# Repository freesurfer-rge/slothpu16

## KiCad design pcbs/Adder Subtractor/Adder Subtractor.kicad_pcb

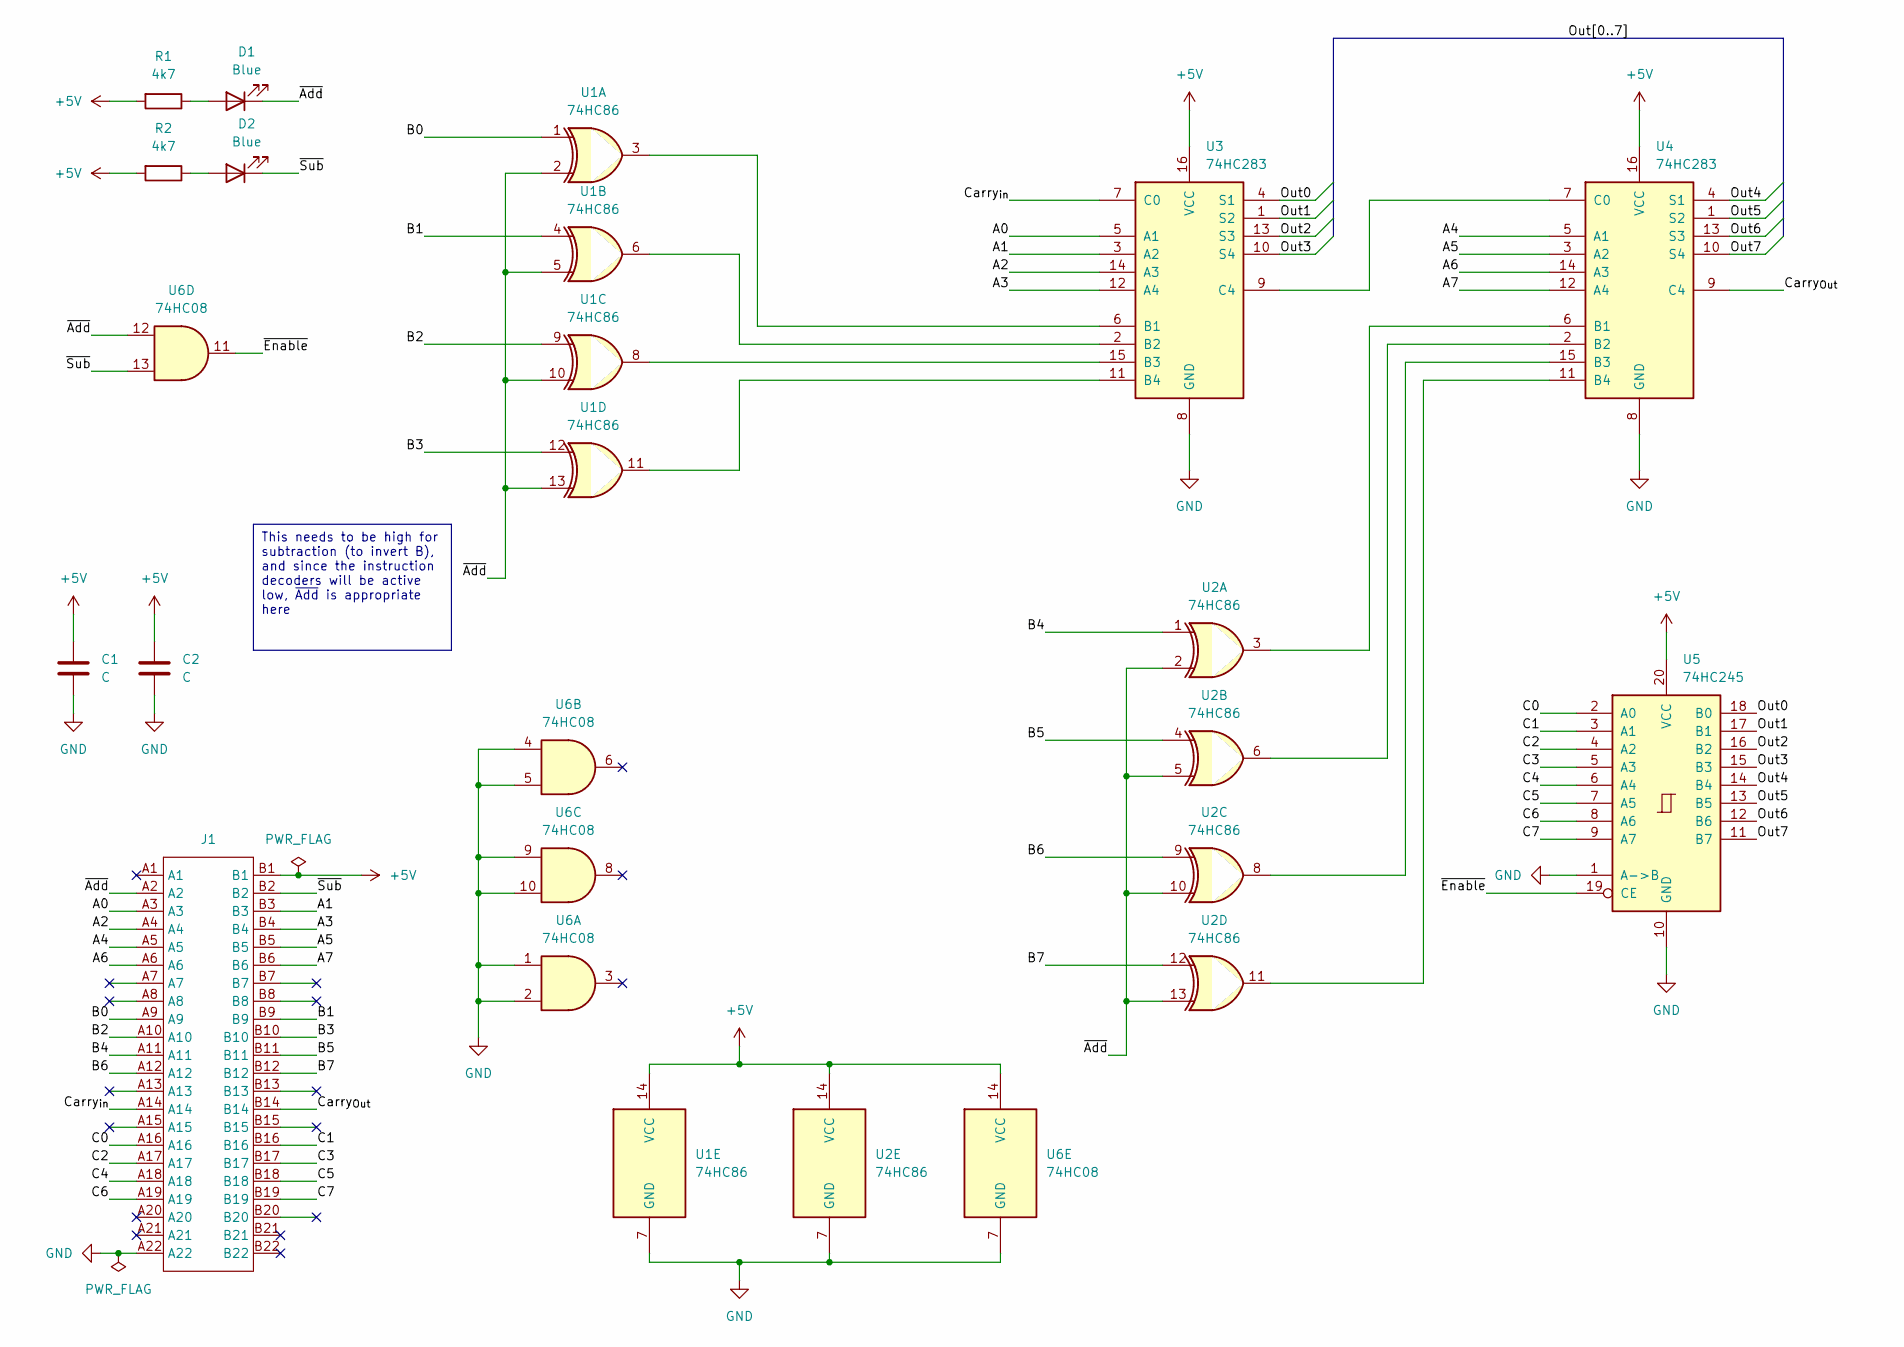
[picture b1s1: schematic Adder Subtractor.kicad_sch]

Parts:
C1, C2: C; C_0603_1608Metric; LCSC C14663
D1, D2: Blue; LED_0603_1608Metric; LCSC C72041
J1: TE-5530843-4-Edge
R1, R2: 4k7; R_0603_1608Metric; LCSC C23162
U1, U2: 74HC86; DIP-14_W7.62mm_Socket
U3, U4: 74HC283; DIP-16_W7.62mm_Socket
U5: 74HC245; SOIC-20W_7.5x12.8mm_P1.27mm; LCSC C5625
U6: 74HC08; SOIC-14_3.9x8.7mm_P1.27mm; LCSC C5593

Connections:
+5V: C1.1, C2.1, J1.B1, R1.2, R2.2, U1.14 (VCC), U2.14 (VCC), U3.16 (VCC), U4.16 (VCC), U5.20 (VCC), U6.14 (VCC)
/A0: J1.A3, U3.5 (A1)
/A1: J1.B3, U3.3 (A2)
/A2: J1.A4, U3.14 (A3)
/A3: J1.B4, U3.12 (A4)
/A4: J1.A5, U4.5 (A1)
/A5: J1.B5, U4.3 (A2)
/A6: J1.A6, U4.14 (A3)
/A7: J1.B6, U4.12 (A4)
/B0: J1.A9, U1.1
/B1: J1.B9, U1.4
/B2: J1.A10, U1.9
/B3: J1.B10, U1.12
/B4: J1.A11, U2.1
/B5: J1.B11, U2.4
/B6: J1.A12, U2.9
/B7: J1.B12, U2.12
/C0: J1.A16, U5.2 (A0)
/C1: J1.B16, U5.3 (A1)
/C2: J1.A17, U5.4 (A2)
/C3: J1.B17, U5.5 (A3)
/C4: J1.A18, U5.6 (A4)
/C5: J1.B18, U5.7 (A5)
/C6: J1.A19, U5.8 (A6)
/C7: J1.B19, U5.9 (A7)
/Carry_{Out}: J1.B14, U4.9 (C4)
/Carry_{in}: J1.A14, U3.7 (C0)
/Out0: U3.4 (S1), U5.18 (B0)
/Out1: U3.1 (S2), U5.17 (B1)
/Out2: U3.13 (S3), U5.16 (B2)
/Out3: U3.10 (S4), U5.15 (B3)
/Out4: U4.4 (S1), U5.14 (B4)
/Out5: U4.1 (S2), U5.13 (B5)
/Out6: U4.13 (S3), U5.12 (B6)
/Out7: U4.10 (S4), U5.11 (B7)
/~Add: D1.1 (K), J1.A2, U1.2, U1.5, U1.10, U1.13, U2.2, U2.5, U2.10, U2.13, U6.12
/~Enable: U5.19 (CE), U6.11
/~Sub: D2.1 (K), J1.B2, U6.13
GND: C1.2, C2.2, J1.A22, U1.7 (GND), U2.7 (GND), U3.8 (GND), U4.8 (GND), U5.1 (A->B), U5.10 (GND), U6.1, U6.2, U6.4, U6.5, U6.7 (GND), U6.9, U6.10
unnamed: D1.2 (A), R1.1
unnamed: D2.2 (A), R2.1
unnamed: U1.3, U3.6 (B1)
unnamed: U1.6, U3.2 (B2)
unnamed: U1.8, U3.15 (B3)
unnamed: U1.11, U3.11 (B4)
unnamed: U3.9 (C4), U4.7 (C0)
unnamed: U2.3, U4.6 (B1)
unnamed: U2.6, U4.2 (B2)
unnamed: U2.8, U4.15 (B3)
unnamed: U2.11, U4.11 (B4)

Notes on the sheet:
This needs to be high for subtraction (to invert B), and since the instruction decoders will be active low, ~{Add} is appropriate here

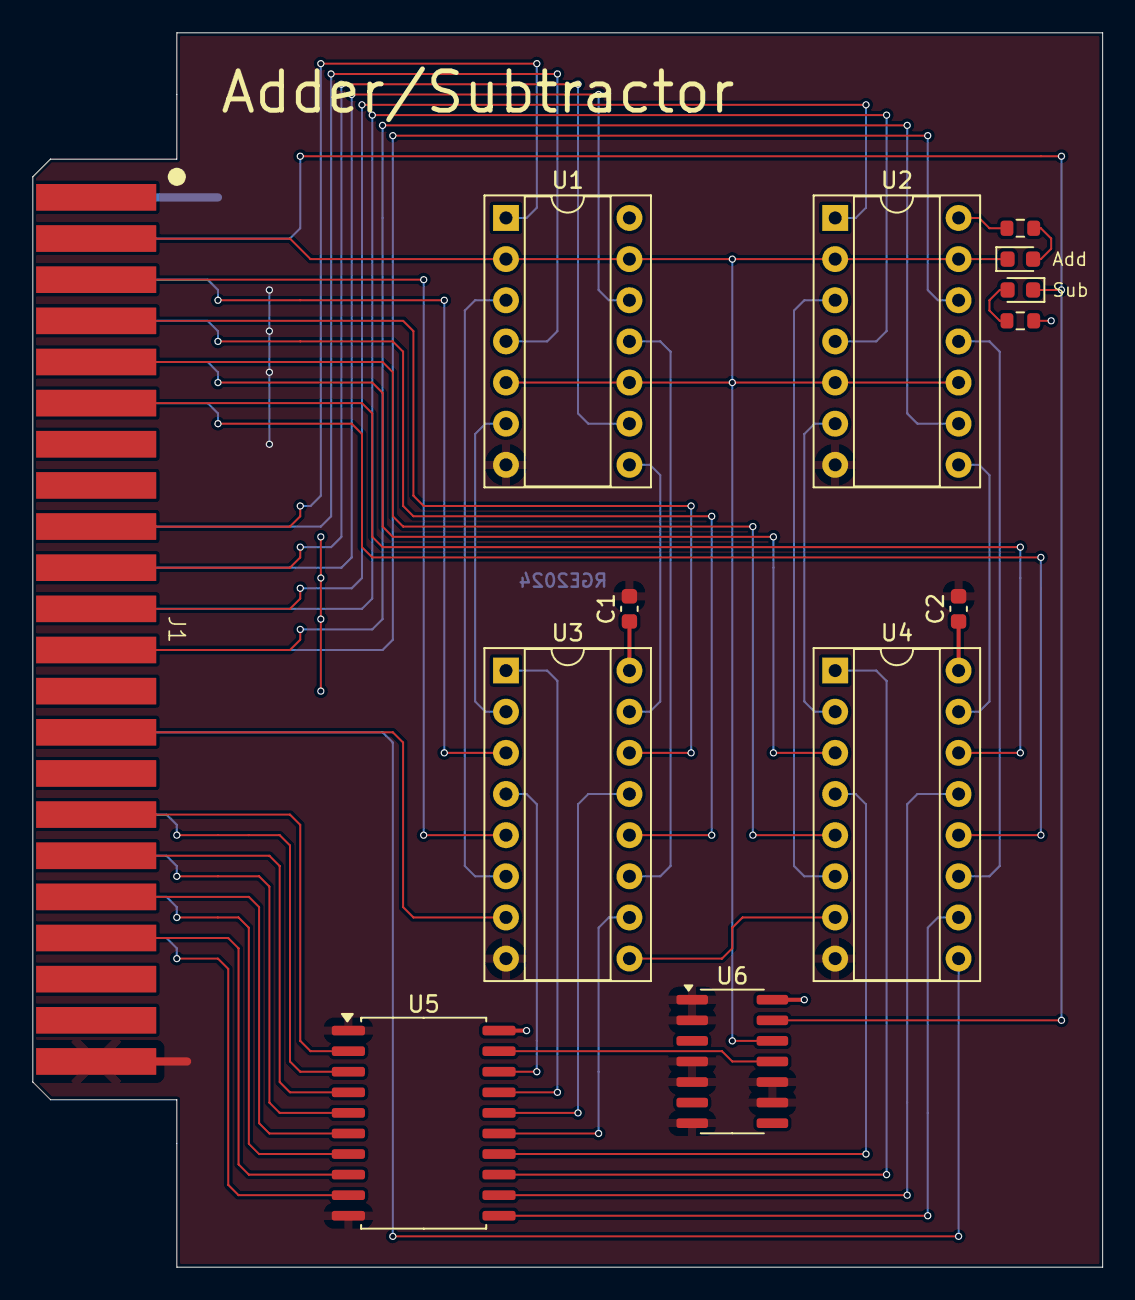
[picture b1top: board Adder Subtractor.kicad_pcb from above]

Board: 2 copper layers, 66.0 x 76.2 mm, 13 parts (0 on the bottom side), 50 nets.

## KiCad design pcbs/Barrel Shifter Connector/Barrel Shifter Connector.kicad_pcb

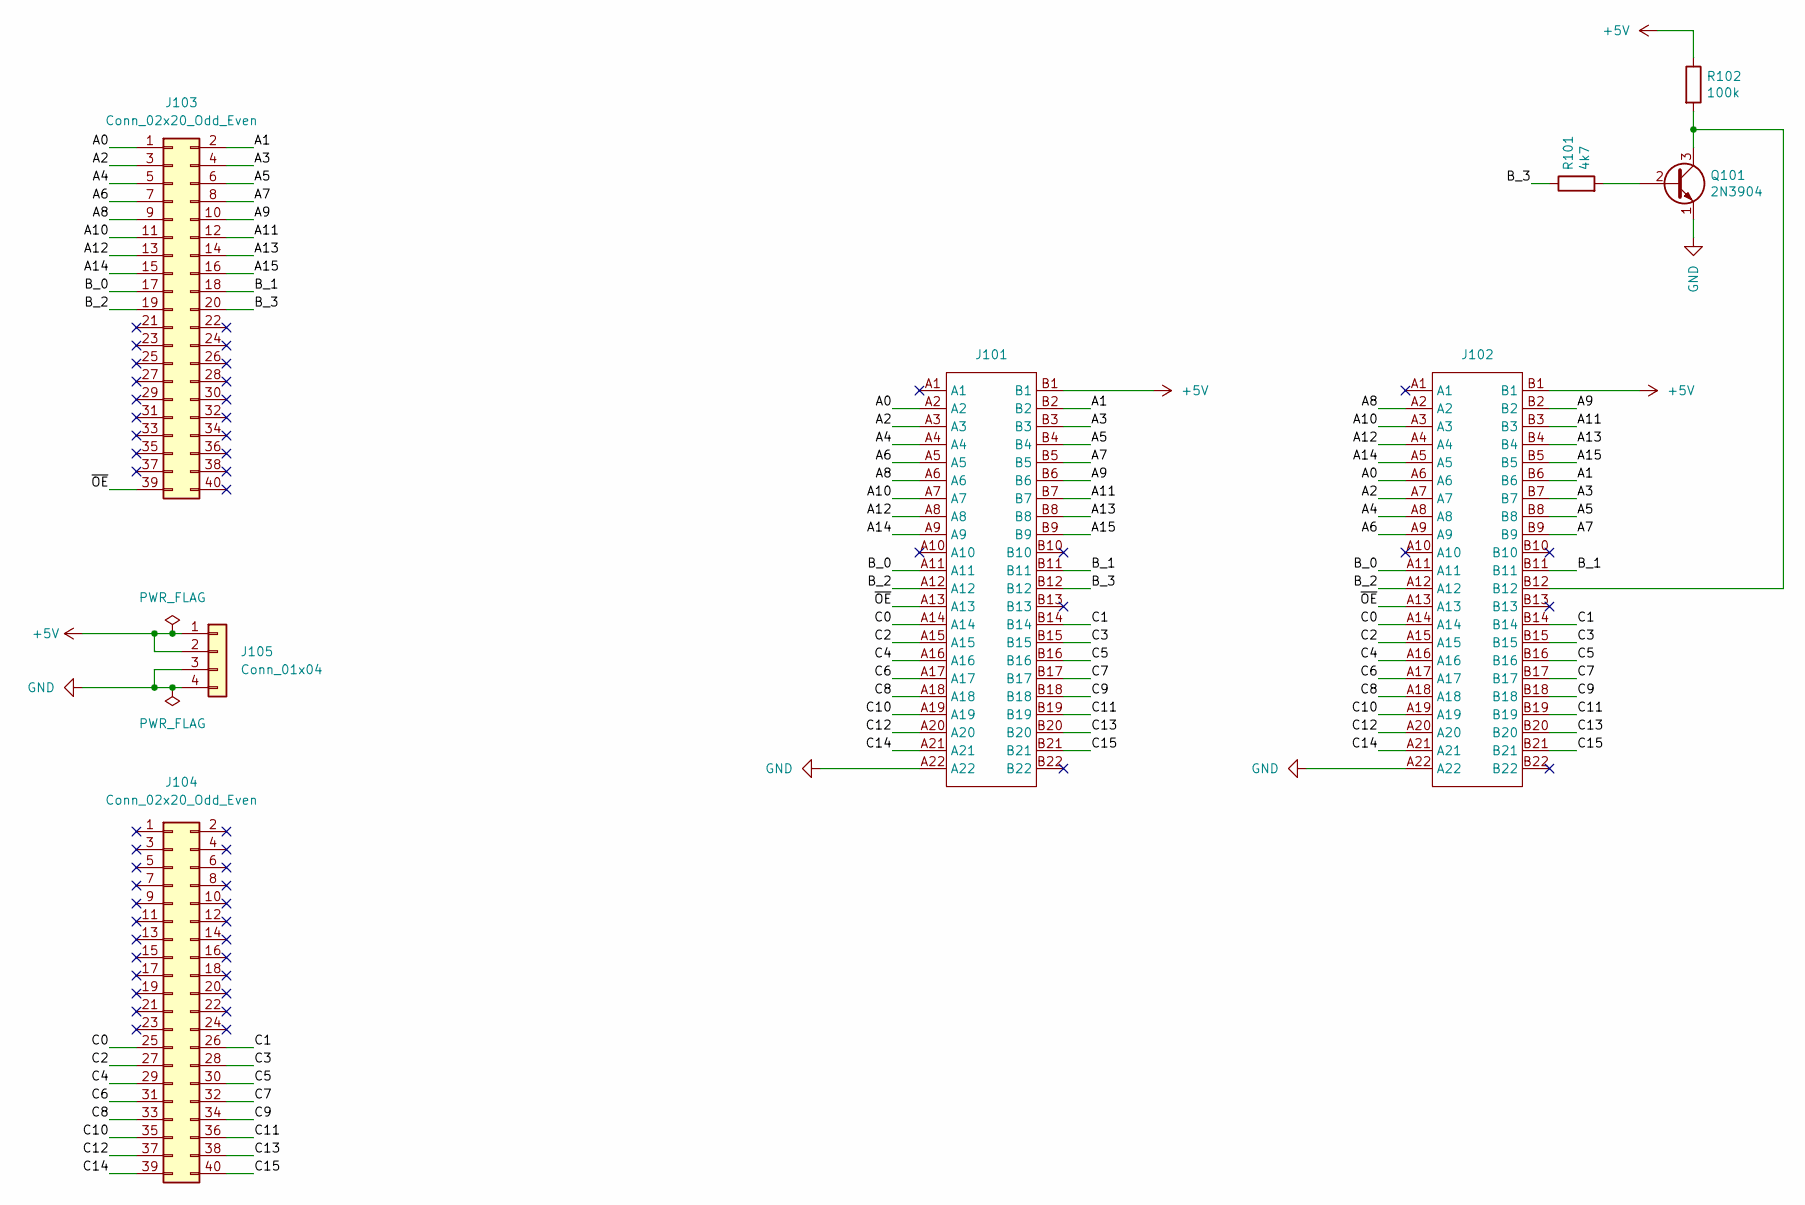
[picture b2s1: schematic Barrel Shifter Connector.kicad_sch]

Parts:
J101, J102: TE-5530843-4-Mount
J103, J104: Conn_02x20_Odd_Even; PinHeader_2x20_P2.54mm_Vertical
J105: Conn_01x04; PinHeader_1x04_P2.54mm_Vertical
Q101: 2N3904; TO-92_Wide
R101: 4k7; R_Axial_DIN0207_L6.3mm_D2.5mm_P7.62mm_Horizontal
R102: 100k; R_Axial_DIN0207_L6.3mm_D2.5mm_P7.62mm_Horizontal

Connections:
+5V: J101.B1, J102.B1, J105.1, J105.2, R102.1
/A0: J101.A2, J102.A6, J103.1
/A1: J101.B2, J102.B6, J103.2
/A2: J101.A3, J102.A7, J103.3
/A3: J101.B3, J102.B7, J103.4
/A4: J101.A4, J102.A8, J103.5
/A5: J101.B4, J102.B8, J103.6
/A6: J101.A5, J102.A9, J103.7
/A7: J101.B5, J102.B9, J103.8
/A8: J101.A6, J102.A2, J103.9
/A9: J101.B6, J102.B2, J103.10
/A10: J101.A7, J102.A3, J103.11
/A11: J101.B7, J102.B3, J103.12
/A12: J101.A8, J102.A4, J103.13
/A13: J101.B8, J102.B4, J103.14
/A14: J101.A9, J102.A5, J103.15
/A15: J101.B9, J102.B5, J103.16
/B_0: J101.A11, J102.A11, J103.17
/B_1: J101.B11, J102.B11, J103.18
/B_2: J101.A12, J102.A12, J103.19
/B_3: J101.B12, J103.20, R101.1
/C0: J101.A14, J102.A14, J104.25
/C1: J101.B14, J102.B14, J104.26
/C2: J101.A15, J102.A15, J104.27
/C3: J101.B15, J102.B15, J104.28
/C4: J101.A16, J102.A16, J104.29
/C5: J101.B16, J102.B16, J104.30
/C6: J101.A17, J102.A17, J104.31
/C7: J101.B17, J102.B17, J104.32
/C8: J101.A18, J102.A18, J104.33
/C9: J101.B18, J102.B18, J104.34
/C10: J101.A19, J102.A19, J104.35
/C11: J101.B19, J102.B19, J104.36
/C12: J101.A20, J102.A20, J104.37
/C13: J101.B20, J102.B20, J104.38
/C14: J101.A21, J102.A21, J104.39
/C15: J101.B21, J102.B21, J104.40
/~OE: J101.A13, J102.A13, J103.39
GND: J101.A22, J102.A22, J105.3, J105.4, Q101.1 (E)
unnamed: Q101.2 (B), R101.2
unnamed: J102.B12, Q101.3 (C), R102.2

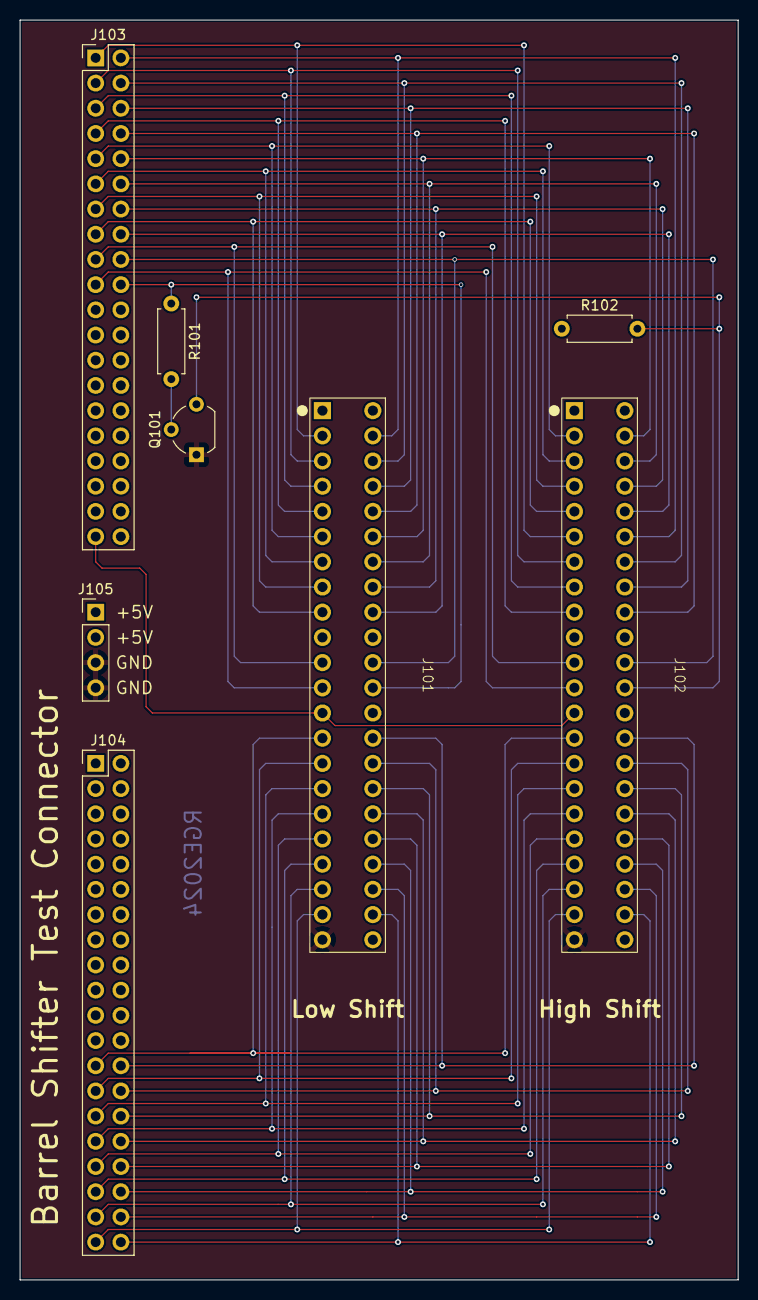
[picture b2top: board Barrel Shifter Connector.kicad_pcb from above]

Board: 2 copper layers, 72.4 x 127.0 mm, 8 parts (0 on the bottom side), 41 nets.

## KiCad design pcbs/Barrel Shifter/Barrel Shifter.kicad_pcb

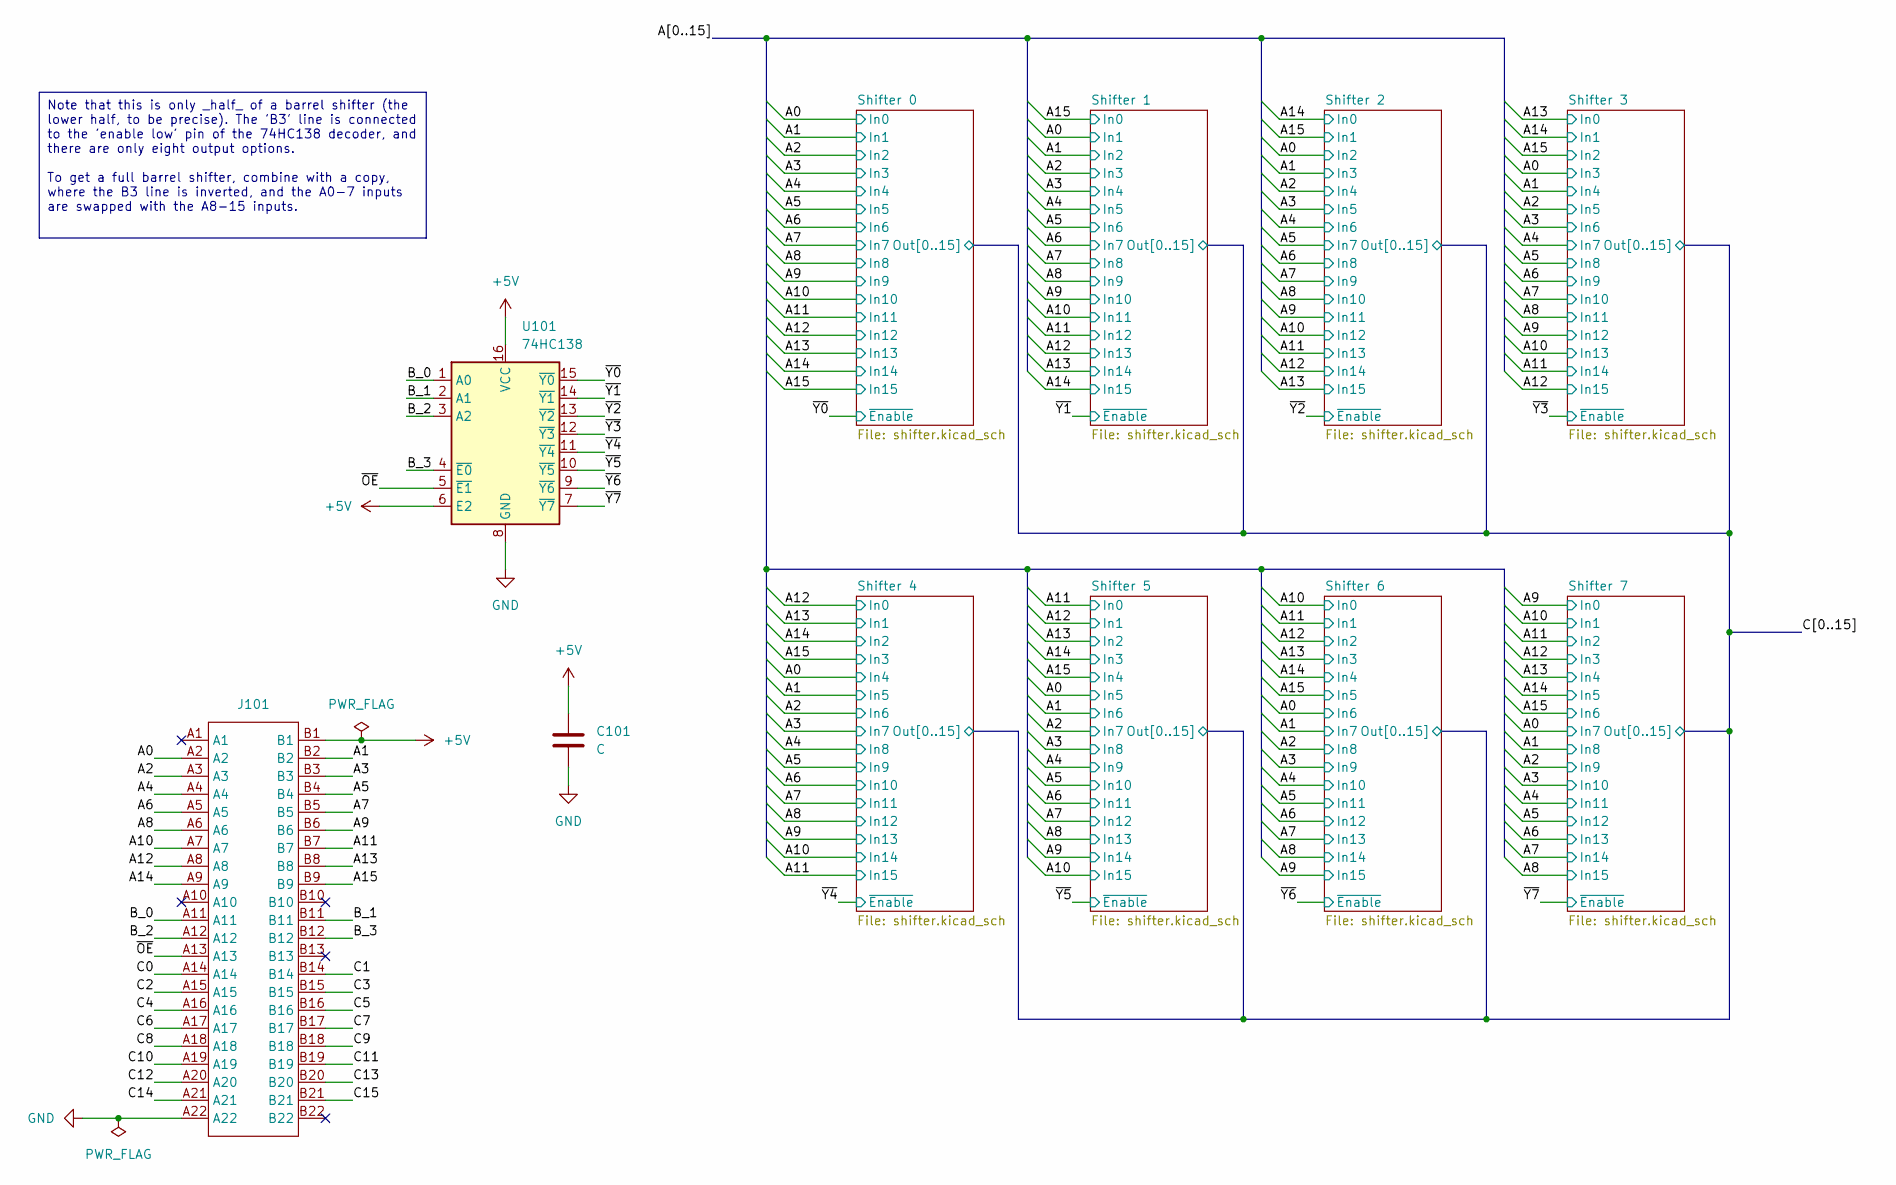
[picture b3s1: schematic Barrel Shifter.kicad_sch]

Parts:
C101: C; C_0603_1608Metric; LCSC C14663
J101: TE-5530843-4-Edge
U101: 74HC138; DIP-16_W7.62mm_Socket

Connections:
+5V: C101.1, J101.B1, U101.6 (E2), U101.16 (VCC); also elsewhere on the board
/A0: J101.A2; also elsewhere on the board
/A1: J101.B2; also elsewhere on the board
/A2: J101.A3; also elsewhere on the board
/A3: J101.B3; also elsewhere on the board
/A4: J101.A4; also elsewhere on the board
/A5: J101.B4; also elsewhere on the board
/A6: J101.A5; also elsewhere on the board
/A7: J101.B5; also elsewhere on the board
/A8: J101.A6; also elsewhere on the board
/A9: J101.B6; also elsewhere on the board
/A10: J101.A7; also elsewhere on the board
/A11: J101.B7; also elsewhere on the board
/A12: J101.A8; also elsewhere on the board
/A13: J101.B8; also elsewhere on the board
/A14: J101.A9; also elsewhere on the board
/A15: J101.B9; also elsewhere on the board
/B_0: J101.A11, U101.1 (A0)
/B_1: J101.B11, U101.2 (A1)
/B_2: J101.A12, U101.3 (A2)
/B_3: J101.B12, U101.4 (~E0)
/C0: J101.A14; also elsewhere on the board
/C1: J101.B14; also elsewhere on the board
/C2: J101.A15; also elsewhere on the board
/C3: J101.B15; also elsewhere on the board
/C4: J101.A16; also elsewhere on the board
/C5: J101.B16; also elsewhere on the board
/C6: J101.A17; also elsewhere on the board
/C7: J101.B17; also elsewhere on the board
/C8: J101.A18; also elsewhere on the board
/C9: J101.B18; also elsewhere on the board
/C10: J101.A19; also elsewhere on the board
/C11: J101.B19; also elsewhere on the board
/C12: J101.A20; also elsewhere on the board
/C13: J101.B20; also elsewhere on the board
/C14: J101.A21; also elsewhere on the board
/C15: J101.B21; also elsewhere on the board
/~OE: J101.A13, U101.5 (~E1)
/~Y0: U101.15 (~Y0); also elsewhere on the board
/~Y1: U101.14 (~Y1); also elsewhere on the board
/~Y2: U101.13 (~Y2); also elsewhere on the board
/~Y3: U101.12 (~Y3); also elsewhere on the board
/~Y4: U101.11 (~Y4); also elsewhere on the board
/~Y5: U101.10 (~Y5); also elsewhere on the board
/~Y6: U101.9 (~Y6); also elsewhere on the board
/~Y7: U101.7 (~Y7); also elsewhere on the board
GND: C101.2, J101.A22, U101.8 (GND); also elsewhere on the board

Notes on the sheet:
Note that this is only _half_ of a barrel shifter (the lower half, to be precise). The 'B3' line is connected to the 'enable low' pin of the 74HC138 decoder, and there are only eight output options. To get a full barrel shifter, combine with a copy, where the B3 line is inverted, and the A0-7 input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

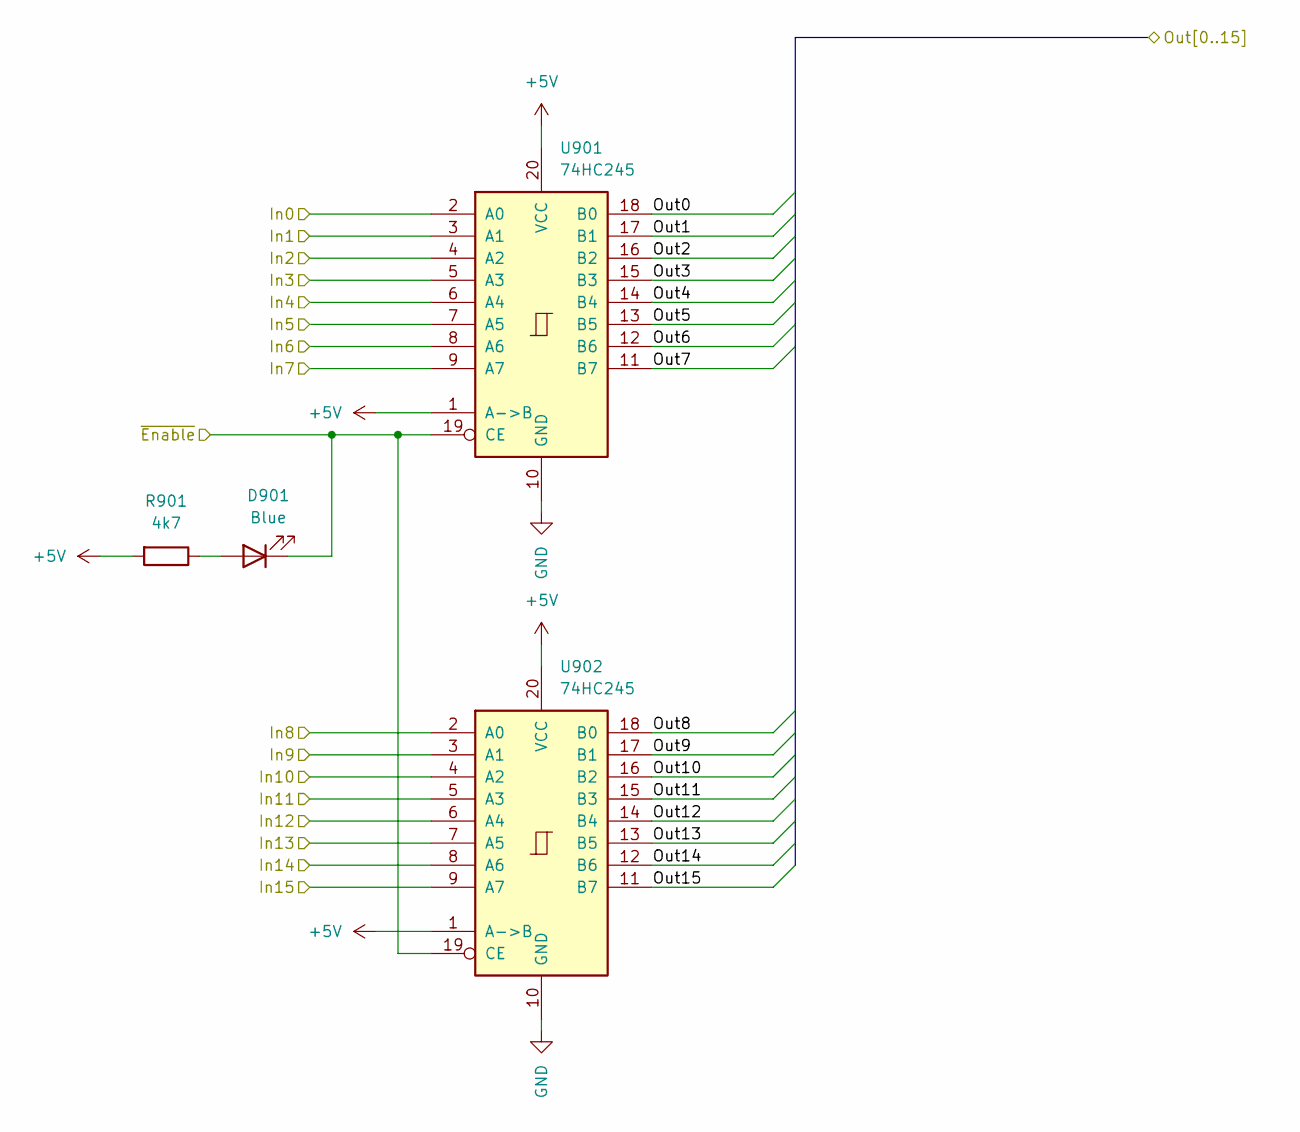
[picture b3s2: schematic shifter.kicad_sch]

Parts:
D901: Blue; LED_0603_1608Metric; LCSC C72041
R901: 4k7; R_0603_1608Metric; LCSC C23162
U901, U902: 74HC245; SOIC-20W_7.5x12.8mm_P1.27mm; LCSC C5625

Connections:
+5V: R901.2, U901.1 (A->B), U901.20 (VCC), U902.1 (A->B), U902.20 (VCC); also elsewhere on the board
/A0: U901.9 (A7); also elsewhere on the board
/A1: U902.2 (A0); also elsewhere on the board
/A2: U902.3 (A1); also elsewhere on the board
/A3: U902.4 (A2); also elsewhere on the board
/A4: U902.5 (A3); also elsewhere on the board
/A5: U902.6 (A4); also elsewhere on the board
/A6: U902.7 (A5); also elsewhere on the board
/A7: U902.8 (A6); also elsewhere on the board
/A8: U902.9 (A7); also elsewhere on the board
/A9: U901.2 (A0); also elsewhere on the board
/A10: U901.3 (A1); also elsewhere on the board
/A11: U901.4 (A2); also elsewhere on the board
/A12: U901.5 (A3); also elsewhere on the board
/A13: U901.6 (A4); also elsewhere on the board
/A14: U901.7 (A5); also elsewhere on the board
/A15: U901.8 (A6); also elsewhere on the board
/C0: U901.18 (B0); also elsewhere on the board
/C1: U901.17 (B1); also elsewhere on the board
/C2: U901.16 (B2); also elsewhere on the board
/C3: U901.15 (B3); also elsewhere on the board
/C4: U901.14 (B4); also elsewhere on the board
/C5: U901.13 (B5); also elsewhere on the board
/C6: U901.12 (B6); also elsewhere on the board
/C7: U901.11 (B7); also elsewhere on the board
/C8: U902.18 (B0); also elsewhere on the board
/C9: U902.17 (B1); also elsewhere on the board
/C10: U902.16 (B2); also elsewhere on the board
/C11: U902.15 (B3); also elsewhere on the board
/C12: U902.14 (B4); also elsewhere on the board
/C13: U902.13 (B5); also elsewhere on the board
/C14: U902.12 (B6); also elsewhere on the board
/C15: U902.11 (B7); also elsewhere on the board
/~Y7: D901.1 (K), U901.19 (CE), U902.19 (CE); also elsewhere on the board
GND: U901.10 (GND), U902.10 (GND); also elsewhere on the board
unnamed: D901.2 (A), R901.1

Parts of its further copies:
D201, D301, D401, D501, D601, D701, D801: Blue; LED_0603_1608Metric; LCSC C72041
R201, R301, R401, R501, R601, R701, R801: 4k7; R_0603_1608Metric; LCSC C23162
U201, U202, U301, U302, U401, U402, U501, U502, U601, U602, U701, U702, U801, U802: 74HC245; SOIC-20W_7.5x12.8mm_P1.27mm; LCSC C5625

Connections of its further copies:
+5V: R201.2, R301.2, R401.2, R501.2, R601.2, R701.2, R801.2, U201.1 (A->B), U201.20 (VCC), U202.1 (A->B), U202.20 (VCC), U301.1 (A->B), U301.20 (VCC), U302.1 (A->B), U302.20 (VCC), U401.1 (A->B), U401.20 (VCC), U402.1 (A->B), U402.20 (VCC), U501.1 (A->B), U501.20 (VCC), U502.1 (A->B), U502.20 (VCC), U601.1 (A->B), U601.20 (VCC), U602.1 (A->B), U602.20 (VCC), U701.1 (A->B), U701.20 (VCC), U702.1 (A->B), U702.20 (VCC), U801.1 (A->B), U801.20 (VCC), U802.1 (A->B), U802.20 (VCC); also elsewhere on the board
/A0: U201.2 (A0), U301.3 (A1), U401.4 (A2), U501.5 (A3), U601.6 (A4), U701.7 (A5), U801.8 (A6); also elsewhere on the board
/A1: U201.3 (A1), U301.4 (A2), U401.5 (A3), U501.6 (A4), U601.7 (A5), U701.8 (A6), U801.9 (A7); also elsewhere on the board
/A2: U201.4 (A2), U301.5 (A3), U401.6 (A4), U501.7 (A5), U601.8 (A6), U701.9 (A7), U802.2 (A0); also elsewhere on the board
/A3: U201.5 (A3), U301.6 (A4), U401.7 (A5), U501.8 (A6), U601.9 (A7), U702.2 (A0), U802.3 (A1); also elsewhere on the board
/A4: U201.6 (A4), U301.7 (A5), U401.8 (A6), U501.9 (A7), U602.2 (A0), U702.3 (A1), U802.4 (A2); also elsewhere on the board
/A5: U201.7 (A5), U301.8 (A6), U401.9 (A7), U502.2 (A0), U602.3 (A1), U702.4 (A2), U802.5 (A3); also elsewhere on the board
/A6: U201.8 (A6), U301.9 (A7), U402.2 (A0), U502.3 (A1), U602.4 (A2), U702.5 (A3), U802.6 (A4); also elsewhere on the board
/A7: U201.9 (A7), U302.2 (A0), U402.3 (A1), U502.4 (A2), U602.5 (A3), U702.6 (A4), U802.7 (A5); also elsewhere on the board
/A8: U202.2 (A0), U302.3 (A1), U402.4 (A2), U502.5 (A3), U602.6 (A4), U702.7 (A5), U802.8 (A6); also elsewhere on the board
/A9: U202.3 (A1), U302.4 (A2), U402.5 (A3), U502.6 (A4), U602.7 (A5), U702.8 (A6), U802.9 (A7); also elsewhere on the board
/A10: U202.4 (A2), U302.5 (A3), U402.6 (A4), U502.7 (A5), U602.8 (A6), U702.9 (A7), U801.2 (A0); also elsewhere on the board
/A11: U202.5 (A3), U302.6 (A4), U402.7 (A5), U502.8 (A6), U602.9 (A7), U701.2 (A0), U801.3 (A1); also elsewhere on the board
/A12: U202.6 (A4), U302.7 (A5), U402.8 (A6), U502.9 (A7), U601.2 (A0), U701.3 (A1), U801.4 (A2); also elsewhere on the board
/A13: U202.7 (A5), U302.8 (A6), U402.9 (A7), U501.2 (A0), U601.3 (A1), U701.4 (A2), U801.5 (A3); also elsewhere on the board
/A14: U202.8 (A6), U302.9 (A7), U401.2 (A0), U501.3 (A1), U601.4 (A2), U701.5 (A3), U801.6 (A4); also elsewhere on the board
/A15: U202.9 (A7), U301.2 (A0), U401.3 (A1), U501.4 (A2), U601.5 (A3), U701.6 (A4), U801.7 (A5); also elsewhere on the board
/C0: U201.18 (B0), U301.18 (B0), U401.18 (B0), U501.18 (B0), U601.18 (B0), U701.18 (B0), U801.18 (B0); also elsewhere on the board
/C1: U201.17 (B1), U301.17 (B1), U401.17 (B1), U501.17 (B1), U601.17 (B1), U701.17 (B1), U801.17 (B1); also elsewhere on the board
/C2: U201.16 (B2), U301.16 (B2), U401.16 (B2), U501.16 (B2), U601.16 (B2), U701.16 (B2), U801.16 (B2); also elsewhere on the board
/C3: U201.15 (B3), U301.15 (B3), U401.15 (B3), U501.15 (B3), U601.15 (B3), U701.15 (B3), U801.15 (B3); also elsewhere on the board
/C4: U201.14 (B4), U301.14 (B4), U401.14 (B4), U501.14 (B4), U601.14 (B4), U701.14 (B4), U801.14 (B4); also elsewhere on the board
/C5: U201.13 (B5), U301.13 (B5), U401.13 (B5), U501.13 (B5), U601.13 (B5), U701.13 (B5), U801.13 (B5); also elsewhere on the board
/C6: U201.12 (B6), U301.12 (B6), U401.12 (B6), U501.12 (B6), U601.12 (B6), U701.12 (B6), U801.12 (B6); also elsewhere on the board
/C7: U201.11 (B7), U301.11 (B7), U401.11 (B7), U501.11 (B7), U601.11 (B7), U701.11 (B7), U801.11 (B7); also elsewhere on the board
/C8: U202.18 (B0), U302.18 (B0), U402.18 (B0), U502.18 (B0), U602.18 (B0), U702.18 (B0), U802.18 (B0); also elsewhere on the board
/C9: U202.17 (B1), U302.17 (B1), U402.17 (B1), U502.17 (B1), U602.17 (B1), U702.17 (B1), U802.17 (B1); also elsewhere on the board
/C10: U202.16 (B2), U302.16 (B2), U402.16 (B2), U502.16 (B2), U602.16 (B2), U702.16 (B2), U802.16 (B2); also elsewhere on the board
/C11: U202.15 (B3), U302.15 (B3), U402.15 (B3), U502.15 (B3), U602.15 (B3), U702.15 (B3), U802.15 (B3); also elsewhere on the board
/C12: U202.14 (B4), U302.14 (B4), U402.14 (B4), U502.14 (B4), U602.14 (B4), U702.14 (B4), U802.14 (B4); also elsewhere on the board
/C13: U202.13 (B5), U302.13 (B5), U402.13 (B5), U502.13 (B5), U602.13 (B5), U702.13 (B5), U802.13 (B5); also elsewhere on the board
/C14: U202.12 (B6), U302.12 (B6), U402.12 (B6), U502.12 (B6), U602.12 (B6), U702.12 (B6), U802.12 (B6); also elsewhere on the board
/C15: U202.11 (B7), U302.11 (B7), U402.11 (B7), U502.11 (B7), U602.11 (B7), U702.11 (B7), U802.11 (B7); also elsewhere on the board
/~Y0: D201.1 (K), U201.19 (CE), U202.19 (CE); also elsewhere on the board
/~Y1: D301.1 (K), U301.19 (CE), U302.19 (CE); also elsewhere on the board
/~Y2: D401.1 (K), U401.19 (CE), U402.19 (CE); also elsewhere on the board
/~Y3: D501.1 (K), U501.19 (CE), U502.19 (CE); also elsewhere on the board
/~Y4: D601.1 (K), U601.19 (CE), U602.19 (CE); also elsewhere on the board
/~Y5: D701.1 (K), U701.19 (CE), U702.19 (CE); also elsewhere on the board
/~Y6: D801.1 (K), U801.19 (CE), U802.19 (CE); also elsewhere on the board
GND: U201.10 (GND), U202.10 (GND), U301.10 (GND), U302.10 (GND), U401.10 (GND), U402.10 (GND), U501.10 (GND), U502.10 (GND), U601.10 (GND), U602.10 (GND), U701.10 (GND), U702.10 (GND), U801.10 (GND), U802.10 (GND); also elsewhere on the board
unnamed: D201.2 (A), R201.1
unnamed: D301.2 (A), R301.1
unnamed: D401.2 (A), R401.1
unnamed: D501.2 (A), R501.1
unnamed: D601.2 (A), R601.1
unnamed: D701.2 (A), R701.1
unnamed: D801.2 (A), R801.1

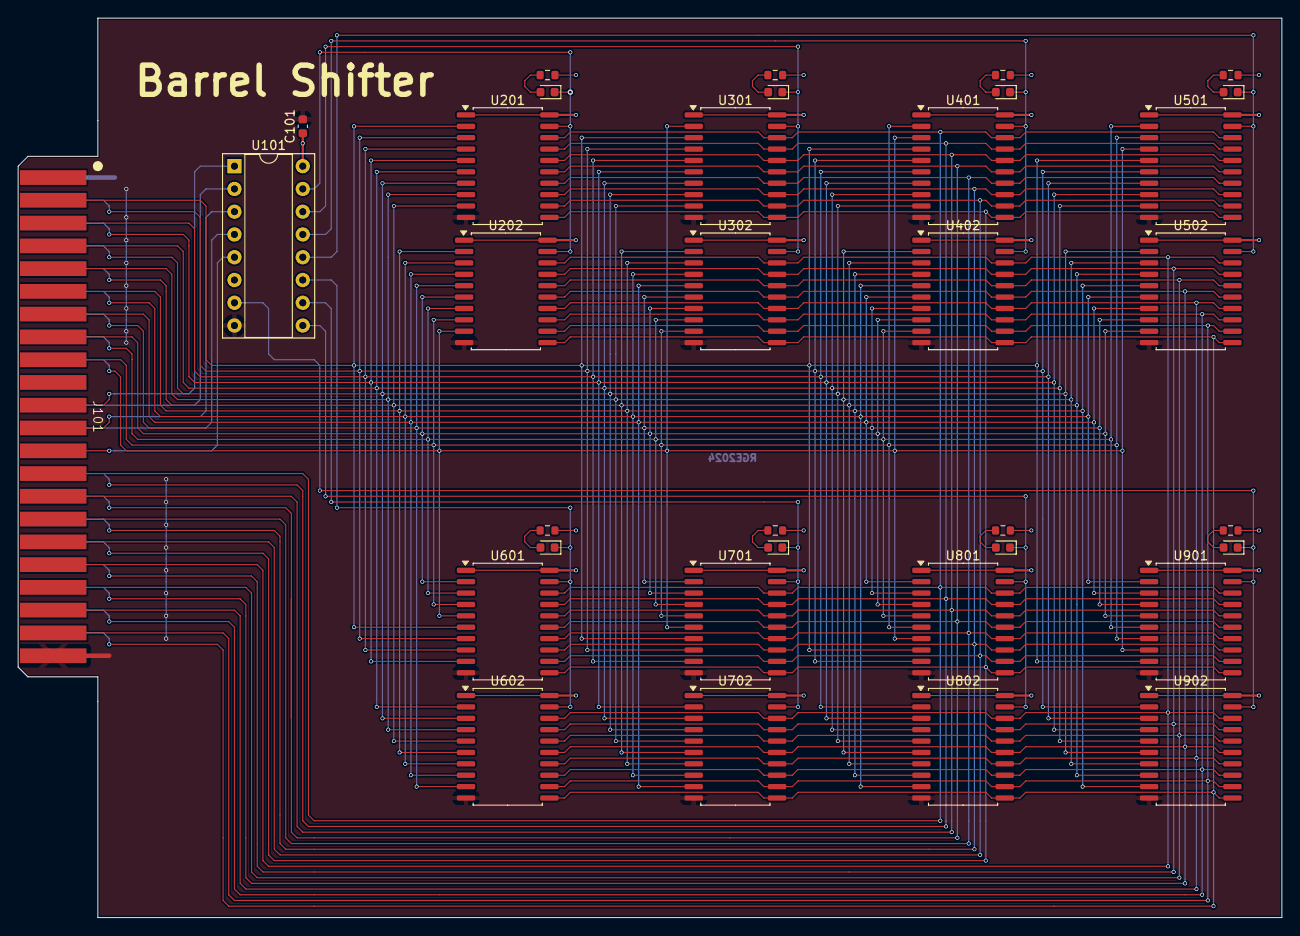
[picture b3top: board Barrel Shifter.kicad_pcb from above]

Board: 2 copper layers, 141.0 x 100.3 mm, 35 parts (0 on the bottom side), 55 nets.
